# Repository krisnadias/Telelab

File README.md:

# Telelab
A collection of resource for making lab equipments that can operate together. Mostly controlled using ESP32 or other microcontrollers that can connect via MQTT to a Node-Red Server

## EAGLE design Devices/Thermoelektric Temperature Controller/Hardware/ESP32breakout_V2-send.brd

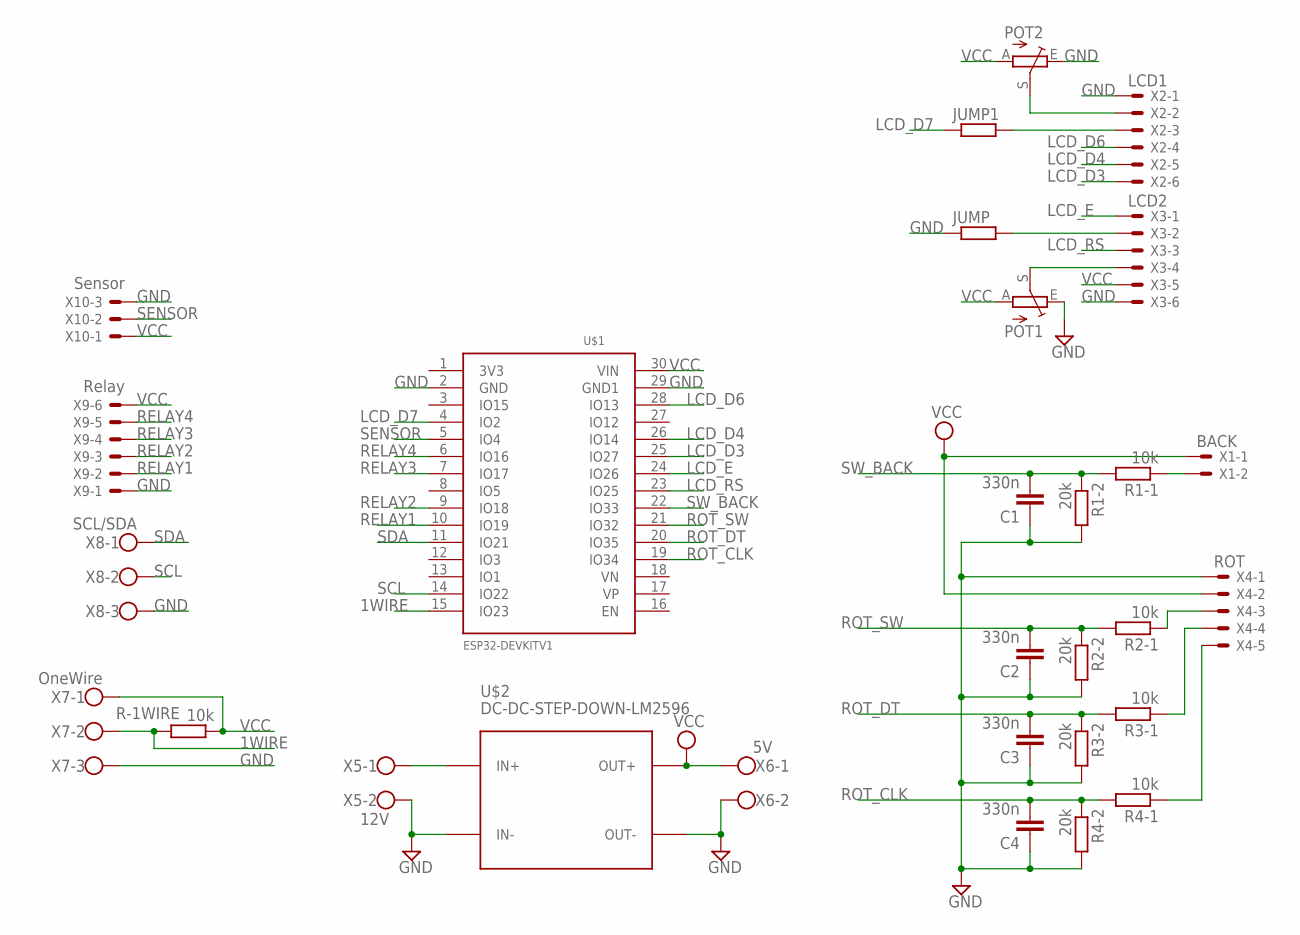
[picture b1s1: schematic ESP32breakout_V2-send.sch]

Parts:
C1, C2, C3, C4: 330n; C025-024X044
JUMP, JUMP1: R-EU_0207/5V; 0207/5V
POT1, POT2: TRIM_EU-CA6V; CA6V
R1-1, R2-1, R3-1, R4-1: 10k; 0204/7
R1-2, R2-2, R3-2, R4-2: 20k; 0204/7
R-1WIRE: 10k; 0204/7
U$1: ESP32DEVKITV1; ESP32-DEVKITV1
U$2: DC-DC-STEP-DOWN-LM2596
X1: BACK; 22-23-2021
X2: LCD1; 22-23-2061
X3: LCD2; 22-23-2061
X4: ROT; 22-23-2051
X5: 12V; W237-102
X6: 5V; W237-102
X7: OneWire; W237-103
X8: SCL/SDA; W237-103
X9: Relay; 22-23-2061
X10: Sensor; 22-23-2031

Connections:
1WIRE: R-1WIRE.2, U$1.15 (IO23), X7.2
GND: C1.1, C2.1, C3.1, C4.1, JUMP.1, POT1.E, POT2.E, R1-2.2, R2-2.2, R3-2.2, R4-2.2, U$1.2 (GND), U$1.29 (GND1), U$2.IN-, U$2.OUT-, X2.1, X3.6, X4.1, X5.2, X6.2, X7.3, X8.3, X9.1, X10.3
LCD_D3: U$1.25 (IO27), X2.6
LCD_D4: U$1.26 (IO14), X2.5
LCD_D6: U$1.28 (IO13), X2.4
LCD_D7: JUMP1.1, U$1.4 (IO2)
LCD_E: U$1.24 (IO26), X3.1
LCD_RS: U$1.23 (IO25), X3.3
unnamed: R1-1.1, X1.2
unnamed: JUMP.2, X3.2
unnamed: U$2.IN+, X5.1
unnamed: R2-1.1, X4.3
unnamed: R3-1.1, X4.4
unnamed: JUMP1.2, X2.3
unnamed: POT2.S, X2.2
unnamed: R4-1.1, X4.5
POT_LCD1: POT1.S, X3.4
RELAY1: U$1.10 (IO19), X9.2
RELAY2: U$1.9 (IO18), X9.3
RELAY3: U$1.7 (IO17), X9.4
RELAY4: U$1.6 (IO16), X9.5
ROT_CLK: C4.2, R4-1.2, R4-2.1, U$1.19 (IO34)
ROT_DT: C3.2, R3-1.2, R3-2.1, U$1.20 (IO35)
ROT_SW: C2.2, R2-1.2, R2-2.1, U$1.21 (IO32)
SCL: U$1.14 (IO22), X8.2
SDA: U$1.11 (IO21), X8.1
SENSOR: U$1.5 (IO4), X10.2
SW_BACK: C1.2, R1-1.2, R1-2.1, U$1.22 (IO33)
VCC: POT1.A, POT2.A, R-1WIRE.1, U$1.30 (VIN), U$2.OUT+, X1.1, X3.5, X4.2, X6.1, X7.1, X9.6, X10.1

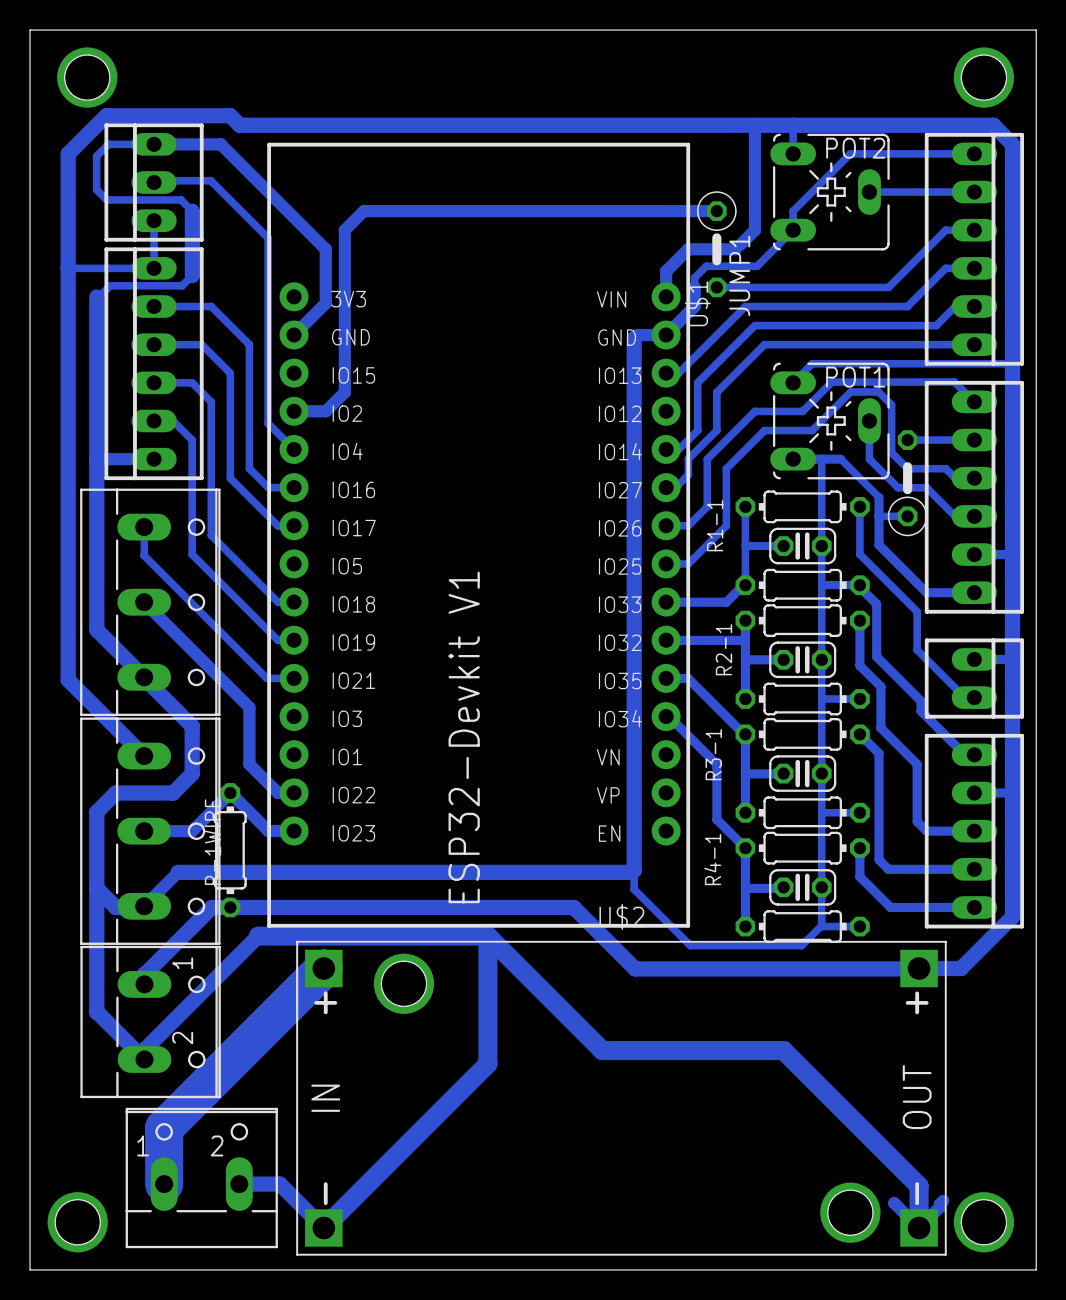
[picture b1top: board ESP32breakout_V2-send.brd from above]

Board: 2 copper layers, 67.0 x 82.5 mm, 29 parts (0 on the bottom side), 29 nets.

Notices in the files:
parts and their libraries:
diy-modules: Released under the Creative Commons Attribution 4.0 International License: http://creativecommons.org/licenses/by/4.0
